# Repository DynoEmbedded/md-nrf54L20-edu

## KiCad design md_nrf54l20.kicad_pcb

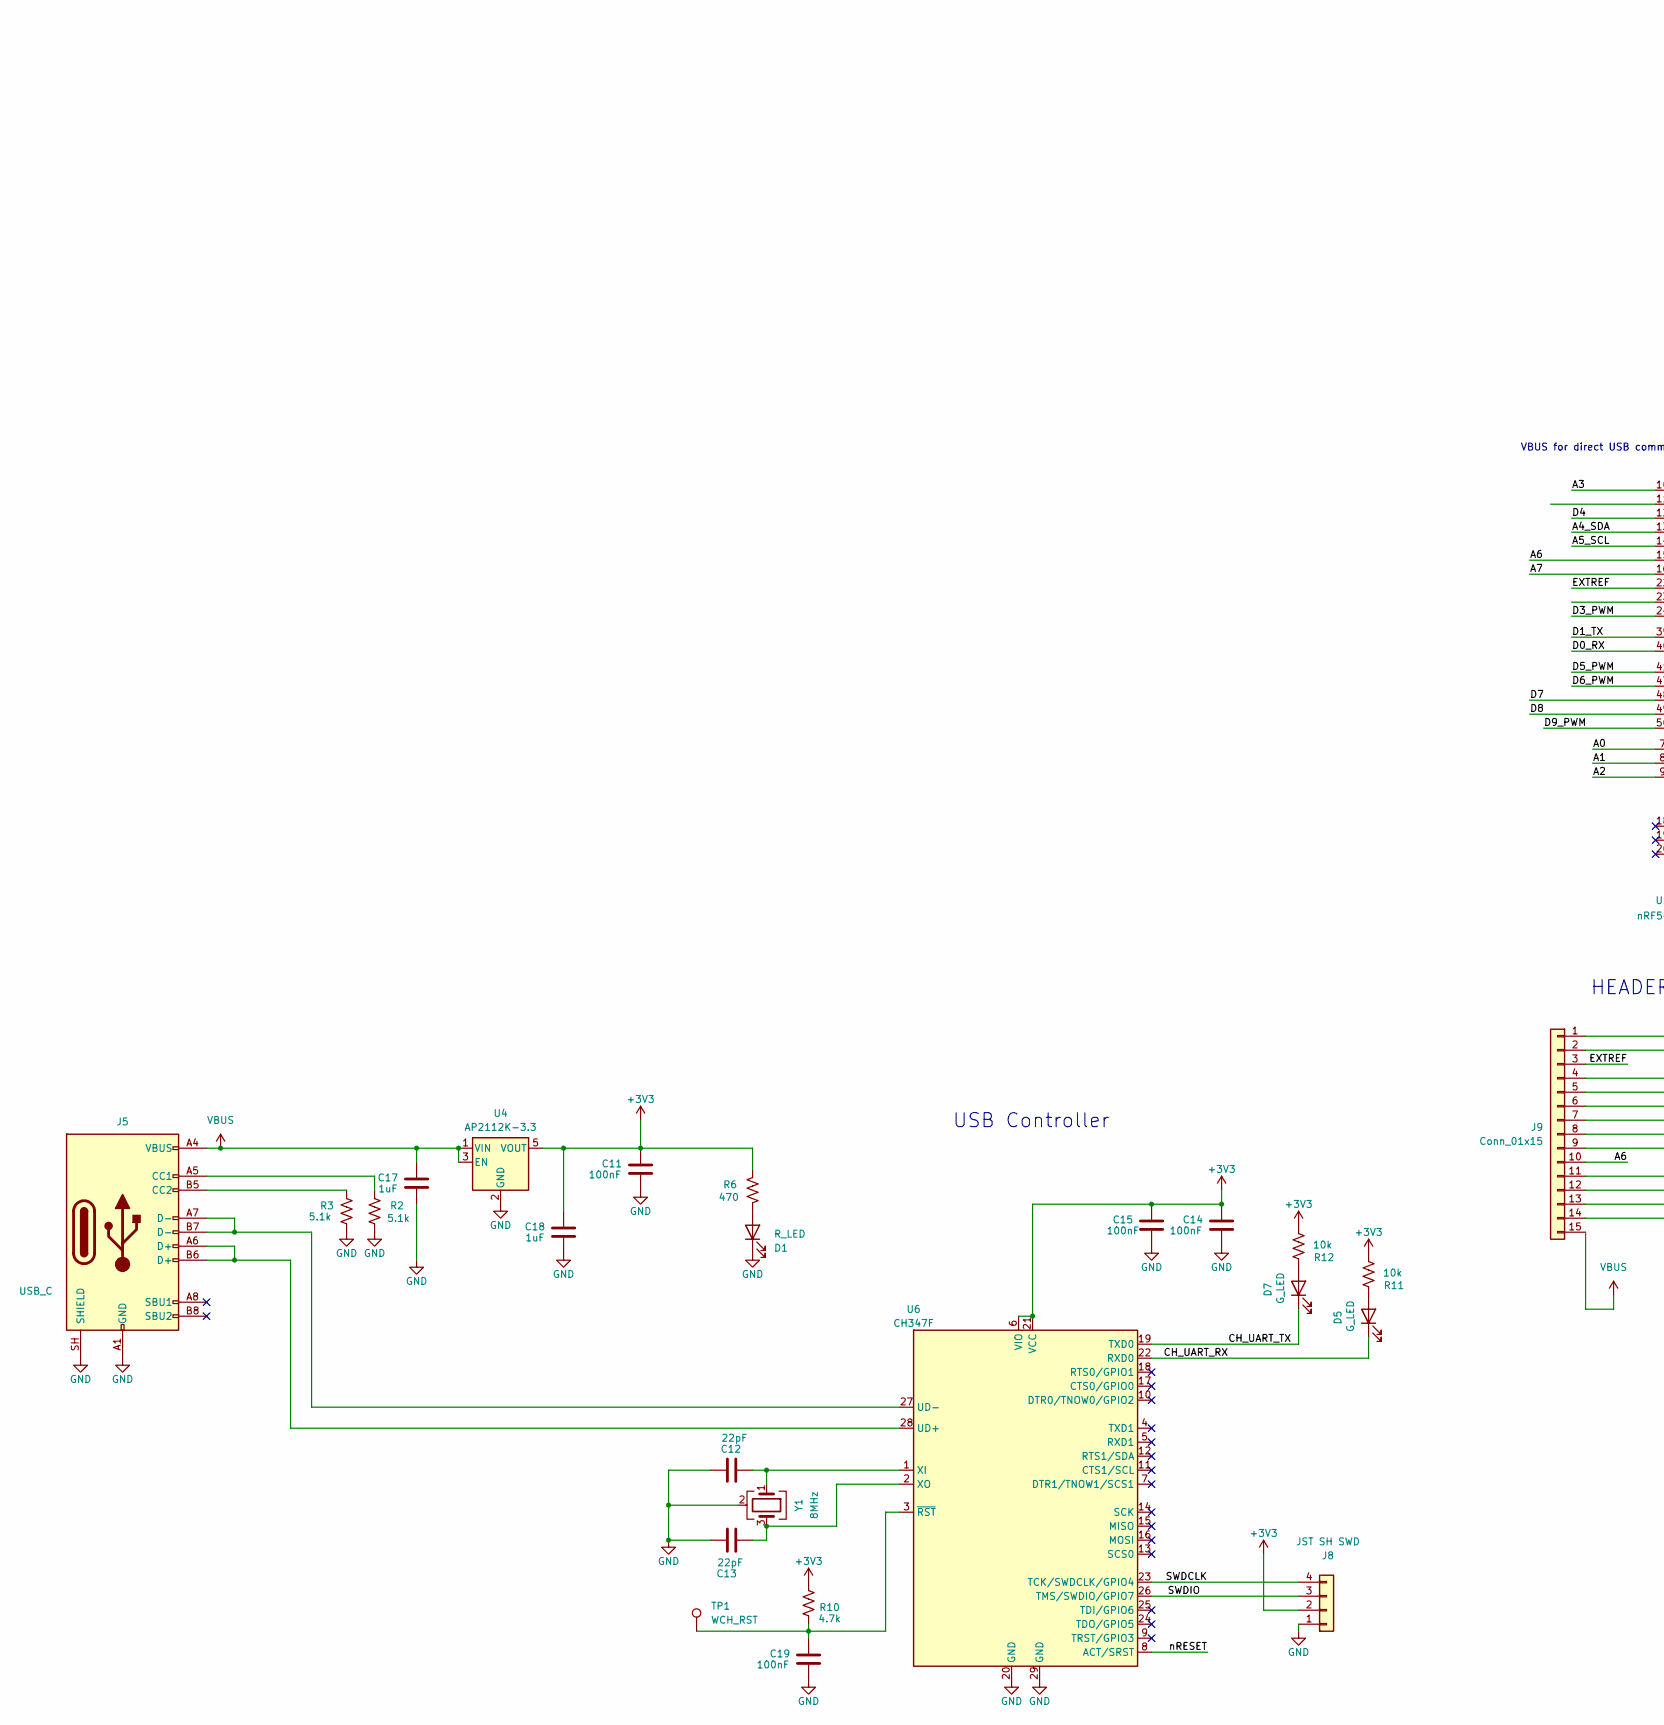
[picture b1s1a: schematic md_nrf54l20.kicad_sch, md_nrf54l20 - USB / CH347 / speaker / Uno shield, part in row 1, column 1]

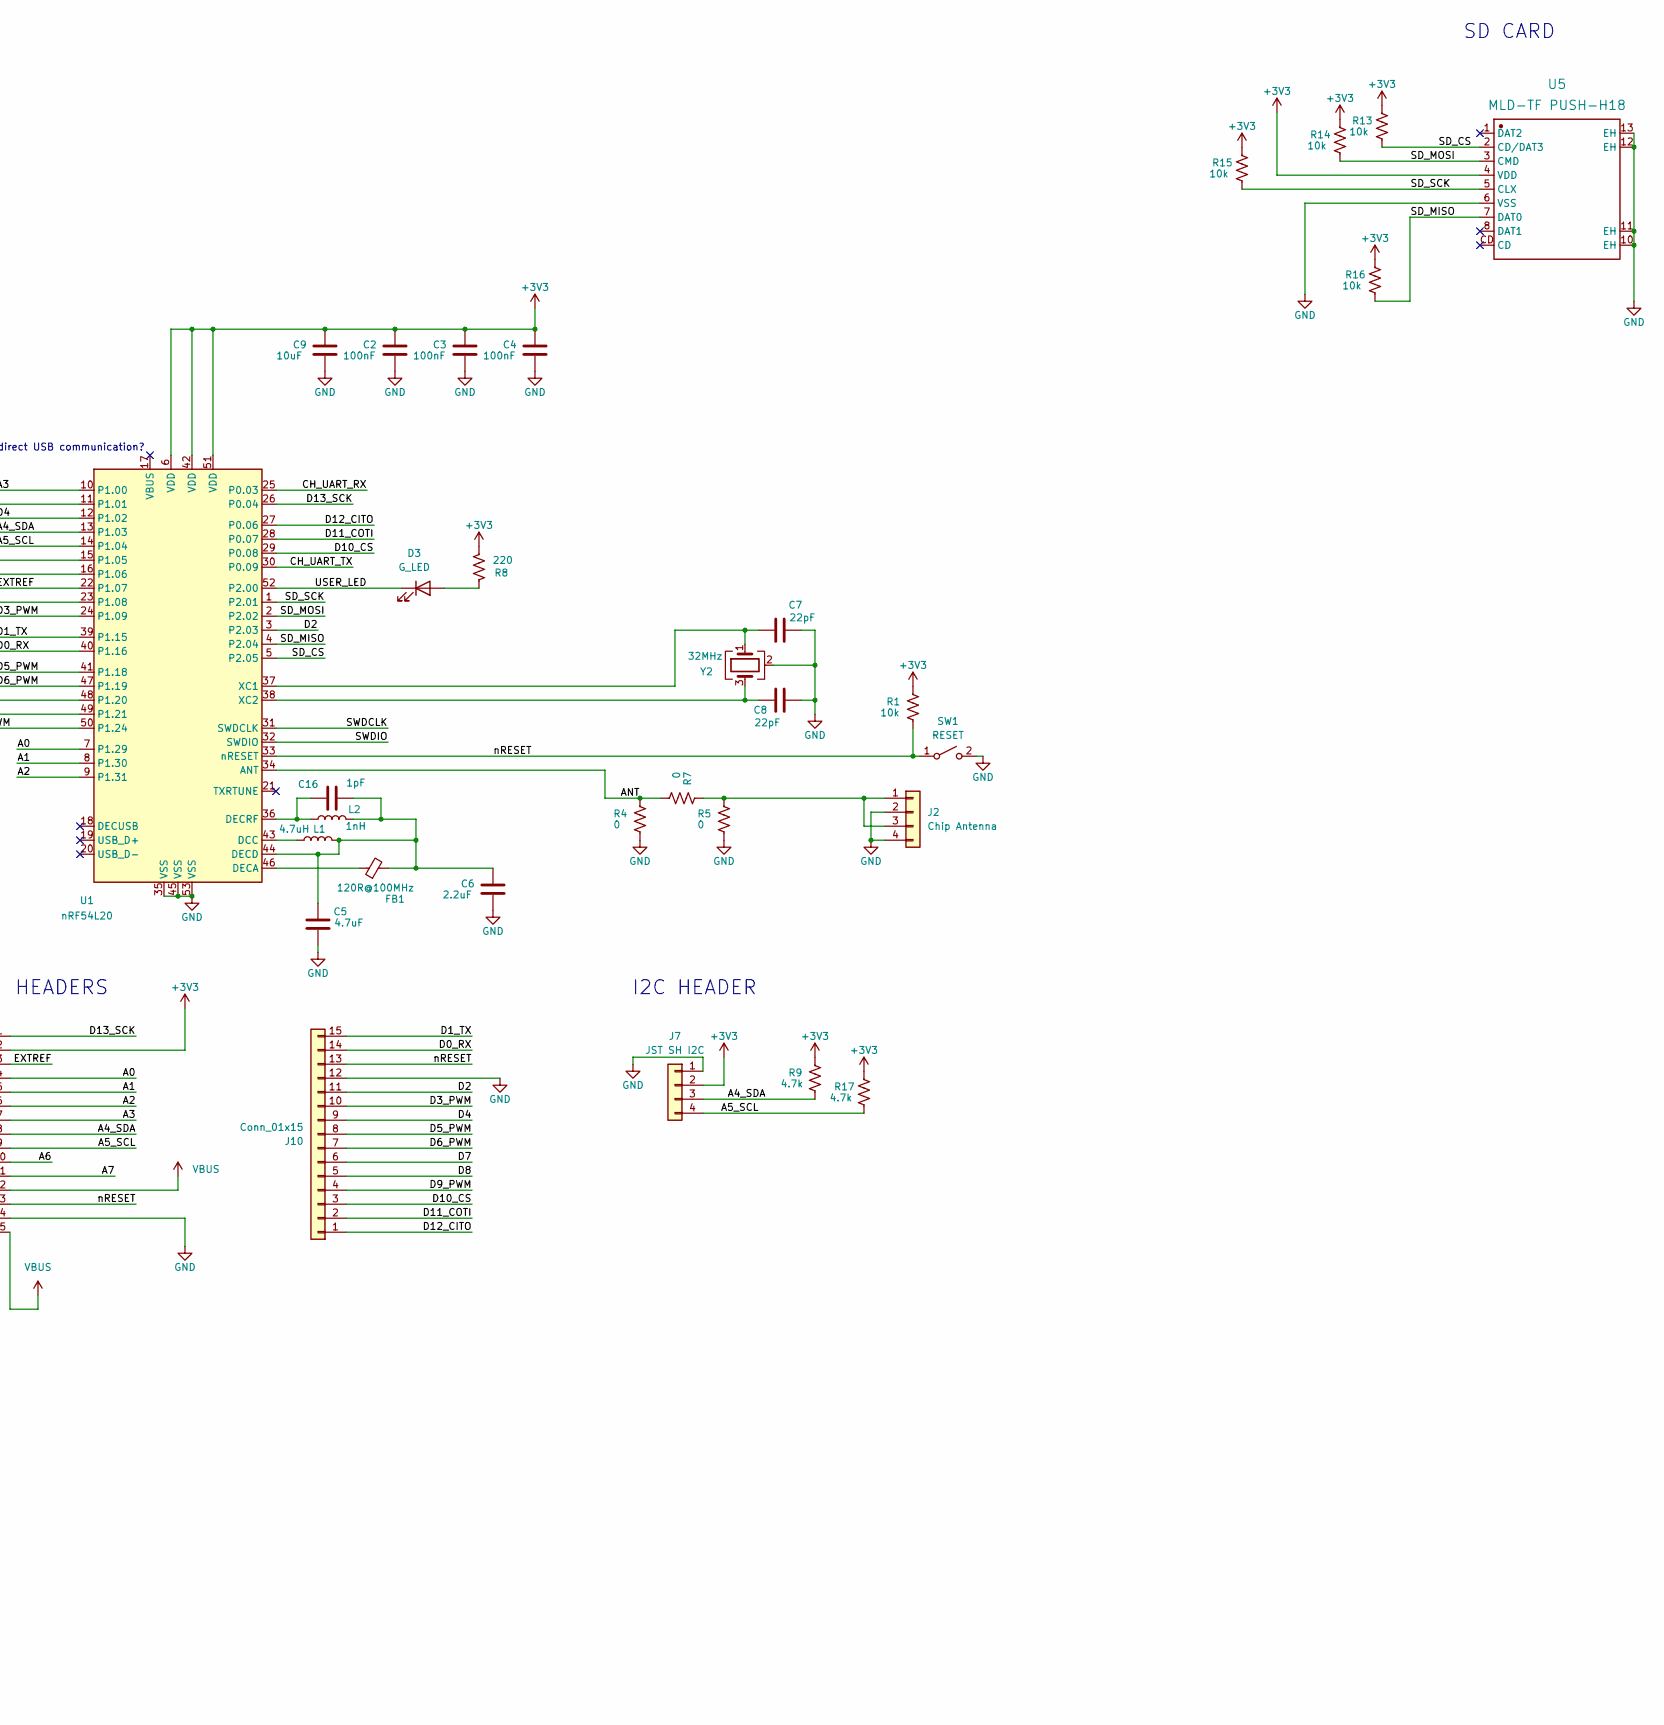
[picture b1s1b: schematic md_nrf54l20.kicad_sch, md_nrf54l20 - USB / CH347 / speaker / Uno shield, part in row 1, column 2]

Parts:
C2, C3, C4, C11, C14, C15, C19: 100nF; C_0402_1005Metric
C5: 4.7uF; C_0402_1005Metric
C6: 2.2uF; C_0402_1005Metric
C7, C8, C12, C13: 22pF; C_0402_1005Metric
C9: 10uF; C_0402_1005Metric
C16: 1pF; C_0402_1005Metric
C17, C18: 1uF; C_0402_1005Metric
D1: R_LED; LED_0402_1005Metric
D3, D5, D7: G_LED; LED_0402_1005Metric
FB1: 120R@100MHz; L_0402_1005Metric
J2: Chip Antenna; Chip Antenna AANI-CH-0070
J5: USB_C; USB_C_Receptacle_HRO_TYPE-C-31-M-12
J7: JST SH I2C; JST_SH_BM04B-SRSS-TB_1x04-1MP_P1.00mm_Vertical
J8: JST SH SWD; JST_SH_BM04B-SRSS-TB_1x04-1MP_P1.00mm_Vertical
J9, J10: Conn_01x15; PinSocket_1x15_P2.54mm_Vertical
L1: 4.7uH; L_0402_1005Metric
L2: 1nH; L_0402_1005Metric
R1, R11, R12, R13, R14, R15, R16: 10k; R_0402_1005Metric
R2, R3: 5.1k; R_0402_1005Metric
R4, R5, R7: 0; R_0402_1005Metric
R6: 470; R_0402_1005Metric
R8: 220; R_0402_1005Metric
R9, R10, R17: 4.7k; R_0402_1005Metric
SW1: RESET; SW-SMD_L3.0-W2.0-LS3.5
TP1: WCH_RST; TestPad-R0.5
U1: nRF54L20; QFN-52-1EP_6x6mm_P0.4mm_EP4.7x4.7mm
U4: AP2112K-3.3; SOT-23-5
U5: MLD-TF PUSH-H18; TF-SMD_MLD-TF-H15; Manufacturer Part MLD-TF PUSH-H18
U6: CH347F; QFN-28-1EP_4x4mm_P0.4mm_EP2.4x2.4mm
Y1: 8MHz; Crystal_SMD_2016-4Pin_2.0x1.6mm
Y2: 32MHz; Crystal_SMD_2016-4Pin_2.0x1.6mm

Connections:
+3V3: C2.1, C3.1, C4.1, C9.1, C11.1, C14.1, C15.1, C18.1, J7.2, J8.2, J9.2, R1.1, R6.1, R8.2, R9.1, R10.1, R11.2, R12.2, R13.1, R14.1, R15.1, R16.1, R17.1, U1.6 (VDD), U1.42 (VDD), U1.51 (VDD), U4.5 (VOUT), U5.4 (VDD), U6.6 (VIO), U6.21 (VCC)
/A0: J9.4, U1.7 (P1.29)
/A1: J9.5, U1.8 (P1.30)
/A2: J9.6, U1.9 (P1.31)
/A3: J9.7, U1.10 (P1.00)
/A4_SDA: J7.3, J9.8, R9.2, U1.13 (P1.03)
/A5_SCL: J7.4, J9.9, R17.2, U1.14 (P1.04)
/A6: J9.10, U1.15 (P1.05)
/A7: J9.11, U1.16 (P1.06)
/ANT: R4.1, R7.2, U1.34 (ANT)
/CH_UART_RX: D5.1 (K), U1.25 (P0.03), U6.22 (RXD0)
/CH_UART_TX: D7.1 (K), U1.30 (P0.09), U6.19 (TXD0)
/D0_RX: J10.14, U1.40 (P1.16)
/D1_TX: J10.15, U1.39 (P1.15)
/D2: J10.11, U1.3 (P2.03)
/D3_PWM: J10.10, U1.24 (P1.09)
/D4: J10.9, U1.12 (P1.02)
/D5_PWM: J10.8, U1.41 (P1.18)
/D6_PWM: J10.7, U1.47 (P1.19)
/D7: J10.6, U1.48 (P1.20)
/D8: J10.5, U1.49 (P1.21)
/D9_PWM: J10.4, U1.50 (P1.24)
/D10_CS: J10.3, U1.29 (P0.08)
/D11_COTI: J10.2, U1.28 (P0.07)
/D12_CITO: J10.1, U1.27 (P0.06)
/D13_SCK: J9.1, U1.26 (P0.04)
/EXTREF: J9.3, U1.22 (P1.07)
/SD_CS: R13.2, U1.5 (P2.05), U5.2 (CD/DAT3)
/SD_MISO: R16.2, U1.4 (P2.04), U5.7 (DAT0)
/SD_MOSI: R14.2, U1.2 (P2.02), U5.3 (CMD)
/SD_SCK: R15.2, U1.1 (P2.01), U5.5 (CLX)
/SWDCLK: J8.4, U1.31 (SWDCLK), U6.23 (TCK/SWDCLK/GPIO4)
/SWDIO: J8.3, U1.32 (SWDIO), U6.26 (TMS/SWDIO/GPIO7)
/USER_LED: D3.1 (K), U1.52 (P2.00)
/nRESET: J9.13, J10.13, R1.2, SW1.1 (A), U1.33 (nRESET), U6.8 (ACT/SRST)
GND: C2.2, C3.2, C4.2, C5.2, C6.2, C7.2, C8.2, C9.2, C11.2, C12.2, C13.2, C14.2, C15.2, C17.2, C18.2, C19.2, D1.1 (K), J2.2, J2.4, J5.A1 (GND), J5.A12 (GND), J5.B1 (GND), J5.B12 (GND), J5.SH (SHIELD), J7.1, J8.1, J9.14, J10.12, R2.2, R3.2, R4.2, R5.2, SW1.2 (B), U1.35 (VSS), U1.45 (VSS), U1.53 (VSS), U4.2 (GND), U5.6 (VSS), U5.10 (EH), U5.11 (EH), U5.12 (EH), U5.13 (EH), U6.20 (GND), U6.29 (GND), Y1.2 (G), Y1.4 (G), Y2.2 (G), Y2.4 (G)
unnamed: D1.2 (A), R6.2
unnamed: D3.2 (A), R8.1
unnamed: D5.2 (A), R11.1
unnamed: D7.2 (A), R12.1
unnamed: J2.1, J2.3, R5.1, R7.1
unnamed: J5.A5 (CC1), R2.1
unnamed: J5.B5 (CC2), R3.1
unnamed: L1.1, U1.43 (DCC)
unnamed: FB1.1, U1.46 (DECA)
unnamed: C5.1, C6.1, C16.2, FB1.2, L1.2, L2.2, U1.44 (DECD)
unnamed: C16.1, L2.1, U1.36 (DECRF)
unnamed: C7.1, U1.37 (XC1), Y2.1
unnamed: C8.1, U1.38 (XC2), Y2.3
unnamed: J5.A6 (D+), J5.B6 (D+), U6.28 (UD+)
unnamed: J5.A7 (D-), J5.B7 (D-), U6.27 (UD-)
unnamed: C12.1, U6.1 (XI), Y1.1
unnamed: C13.1, U6.2 (XO), Y1.3
unnamed: C19.1, R10.2, TP1.1 (1_1), U6.3 (~RST)
VBUS: C17.1, J5.A4 (VBUS), J5.A9 (VBUS), J5.B4 (VBUS), J5.B9 (VBUS), J9.12, J9.15, U4.1 (VIN), U4.3 (EN)

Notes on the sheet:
USB Controller
VBUS for direct USB communication?
SD CARD
I2C HEADER
HEADERS

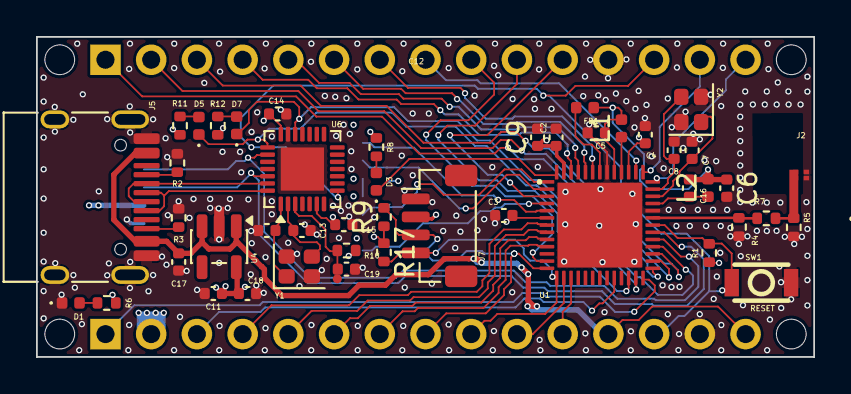
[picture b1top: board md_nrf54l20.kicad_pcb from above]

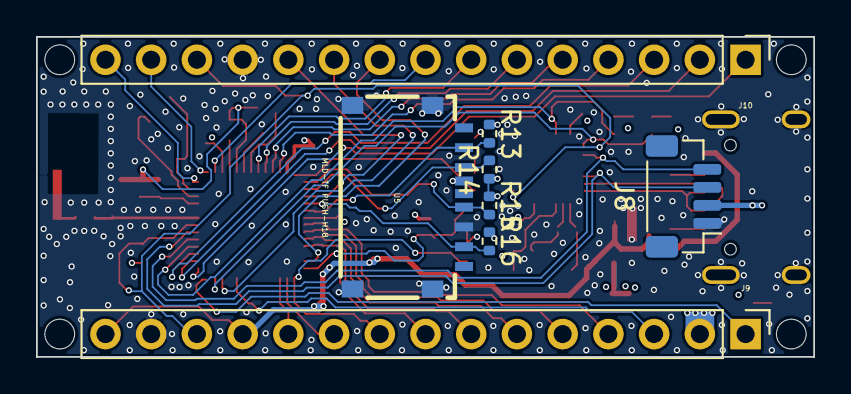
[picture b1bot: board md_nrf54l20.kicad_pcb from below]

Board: 4 copper layers, 43.2 x 17.8 mm, 59 parts (8 on the bottom side), 55 nets.

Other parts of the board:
MH1, MH2, MH3, MH4: MountingHole_65mil

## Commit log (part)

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2026-06-06 Setup projec
2026-06-06 Update symbols
2026-06-07 Update file names
2026-06-18 Update layout
2026-06-19 Fix nets in schematic
2026-06-19 Add caps to pcb
2026-06-19 Update components
2026-06-19 Swap most 0603 to 0402
2026-06-19 Remove 10uf filter cap
2026-06-19 Layout work
2026-06-19 Layout work, all main components on board
2026-06-20 Pre-flip routing
2026-06-20 Post flip routing
2026-06-20 More routing
2026-06-20 More routing, swap jst sh to vertical
2026-06-29 Edit board setup
2026-06-29 Swap mcu direction
